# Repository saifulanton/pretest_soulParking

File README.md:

# PRE TEST INTERVIEW PT SOUL PARKING
Merupakan Syarat yang kerjakan sebelum interview untuk melihat kompetensi dasar pelamar

# Repository ini berisi dari 3 folder yaitu :
1. Soal Pre-test
2. Layout PCB terdiri dari Skematik dan Board Eagle 9 dan Gambar Tampak Atas dan Bawah Rangkaian Soal Pre-Test
3. Program Arduino

# Software dan library yang harus diinstall
1. Arduinio IDE
   a. library LCD I2C ==> https://www.dropbox.com/s/asp8w5ja64bn7u9/Arduino-LiquidCrystal-I2C-library-master.zip
   b. library DHT ==> https://github.com/adafruit/DHT-sensor-library/archive/master.zip
   c. Adafruit Unified Sensor ==> Buka Arduino IDE > klik menu Sketch > sub menu include library > Manage libraries > search dan install "Adafruit Unified Sensor"
   
2. Eagle 9 ==> untuk membuka dokumen skematik dan board rangkaian ataupun PCB

# Bill Of Material
1. Jack Dc Female
2. Terminal Block 2 pin
3. dioda 1n4004 (1 Ampere)
4. IC Regulator +5V (LM7805)
5. Capasitor non polar type MKM (100nF)
6. Capasitor Elco 10uF
7. Resistor 220Ohm For LED
8. Resistor 1k For R Basis Transistor Switching
9. Transistor NPN Type BD139
10. pin Header Male 1x3 For DHT
11. pin Header Male 1x4 For LCD I2C
12. LCD I2C 16x2
13. DHT 11
14. Arduino Nano Board V.3
15. Buzzer 5V
16. LED 5mm
17. Cable USB Mini USB For Arduino Nano
18. Cable Female to Female 
19. Adaptor +12V 
20. PCB
21. Spacer

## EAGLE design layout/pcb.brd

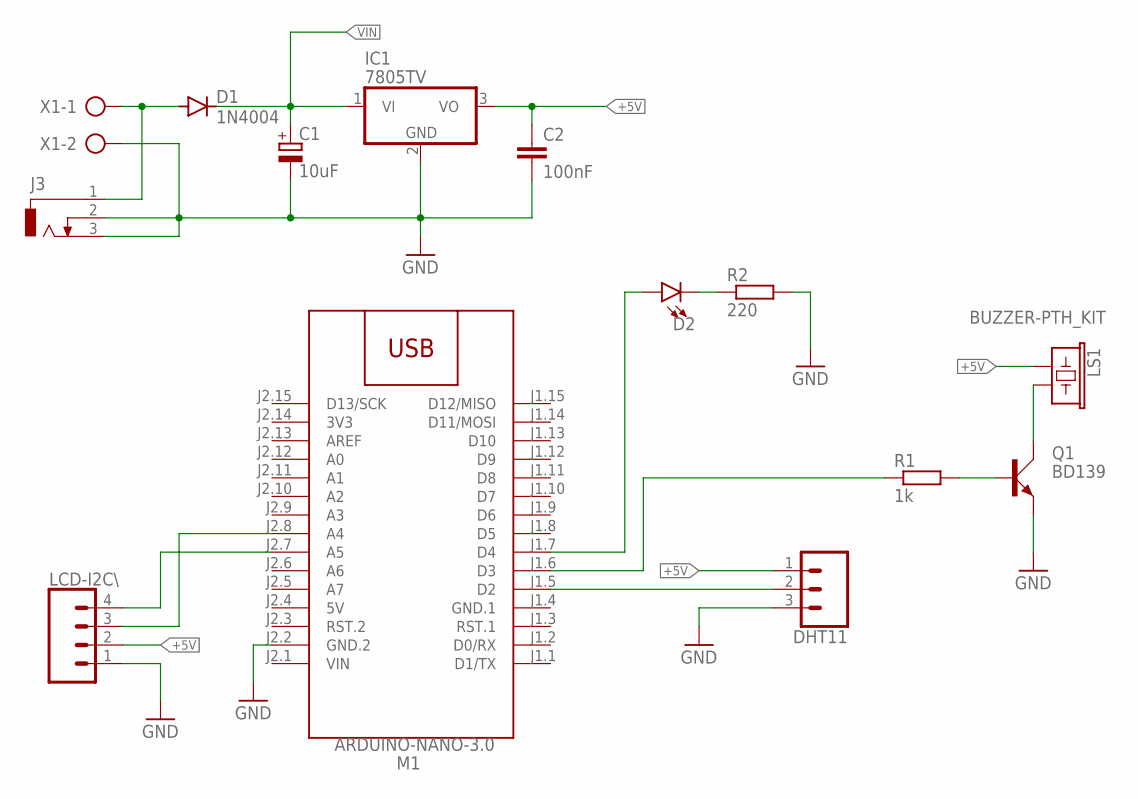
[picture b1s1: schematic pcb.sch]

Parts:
C1: 10uF; E2,5-6
C2: 100nF; C050-025X075
D1: 1N4004; DO41-10
D2: LED5MM; LED_5MM
DHT11: CONN_03LONGPADS; 1X03_LONGPADS
IC1: 7805TV; TO220V
J3: DCJ0303
LCD-I2C\: CONN_04LONGPADS; 1X04_LONGPADS
LS1: BUZZER-PTH_KIT; BUZZER-12MM-KIT
M1: ARDUINO-NANO-3.0
Q1: BD139; TO126AV
R1: 1k; 0207/10
R2: 220; 0207/10
X1: AK300/2

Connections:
3V3: M1.J2.14 (3V3)
5V: M1.J2.4 (5V)
+5V: C2.1, DHT11.1, IC1.3 (VO), LCD-I2C\.2, LS1.+ (1)
GND: C1.-, C2.2, DHT11.3, IC1.2 (GND), J3.2, J3.3, LCD-I2C\.1, M1.J2.2 (GND.2), Q1.E, R2.2, X1.2
GND.1: M1.J1.4 (GND.1)
unnamed: M1.J1.6 (D3), R1.1
unnamed: DHT11.2, M1.J1.5 (D2)
unnamed: LCD-I2C\.4, M1.J2.7 (A5)
unnamed: D1.A, J3.1, X1.1
unnamed: LCD-I2C\.3, M1.J2.8 (A4)
unnamed: Q1.B, R1.2
unnamed: LS1.- (2), Q1.C
unnamed: D2.K (C), R2.1
unnamed: D2.A, M1.J1.7 (D4)
VIN: C1.+, D1.C, IC1.1 (VI), M1.J2.1 (VIN)

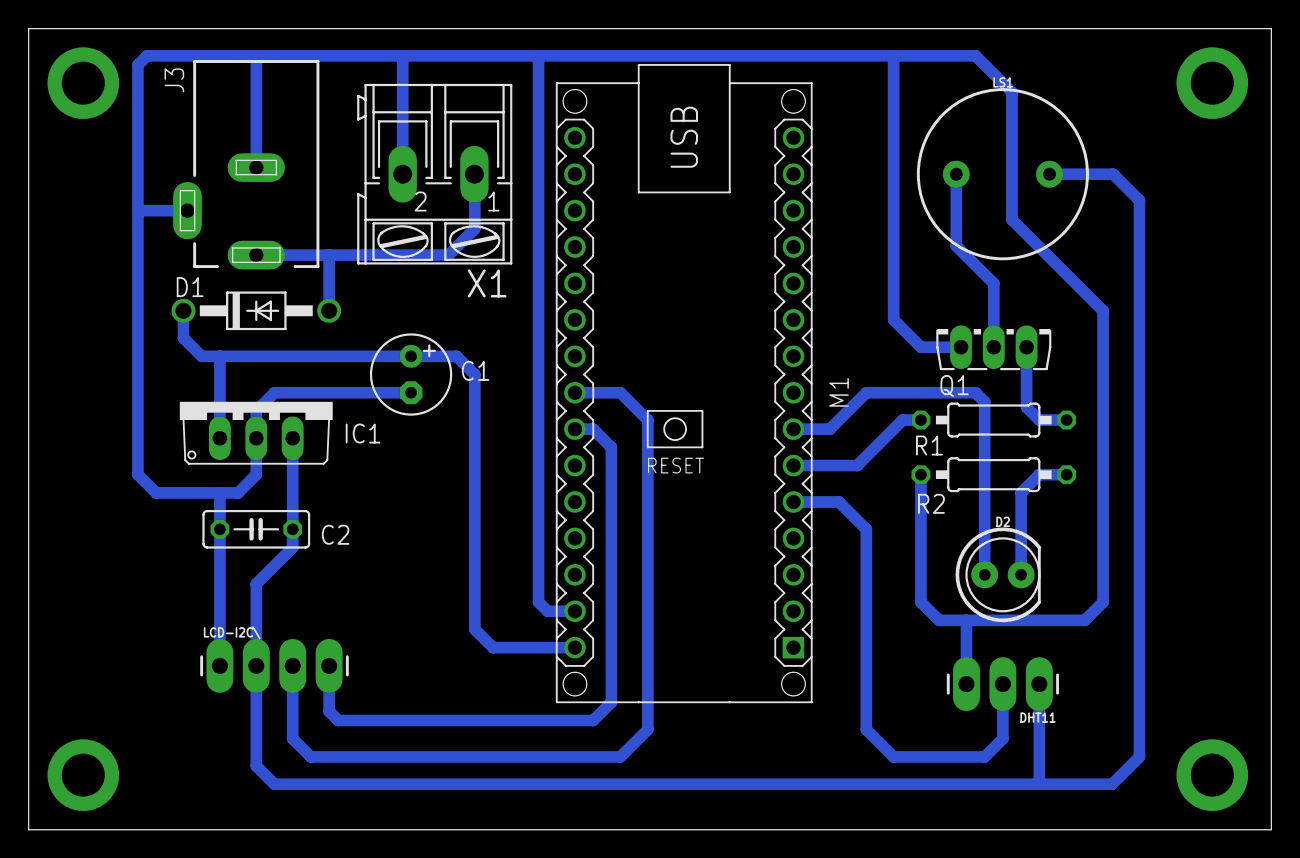
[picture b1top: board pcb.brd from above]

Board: 2 copper layers, 86.7 x 55.9 mm, 14 parts (0 on the bottom side), 12 nets.

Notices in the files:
parts and their libraries:
SparkFun-LED: Licensing: Creative Commons ShareAlike 4.0 International - https://creativecommons.org/licenses/by-sa/4.0
diy-modules: Released under the Creative Commons Attribution 4.0 International License: http://creativecommons.org/licenses/by/4.0
